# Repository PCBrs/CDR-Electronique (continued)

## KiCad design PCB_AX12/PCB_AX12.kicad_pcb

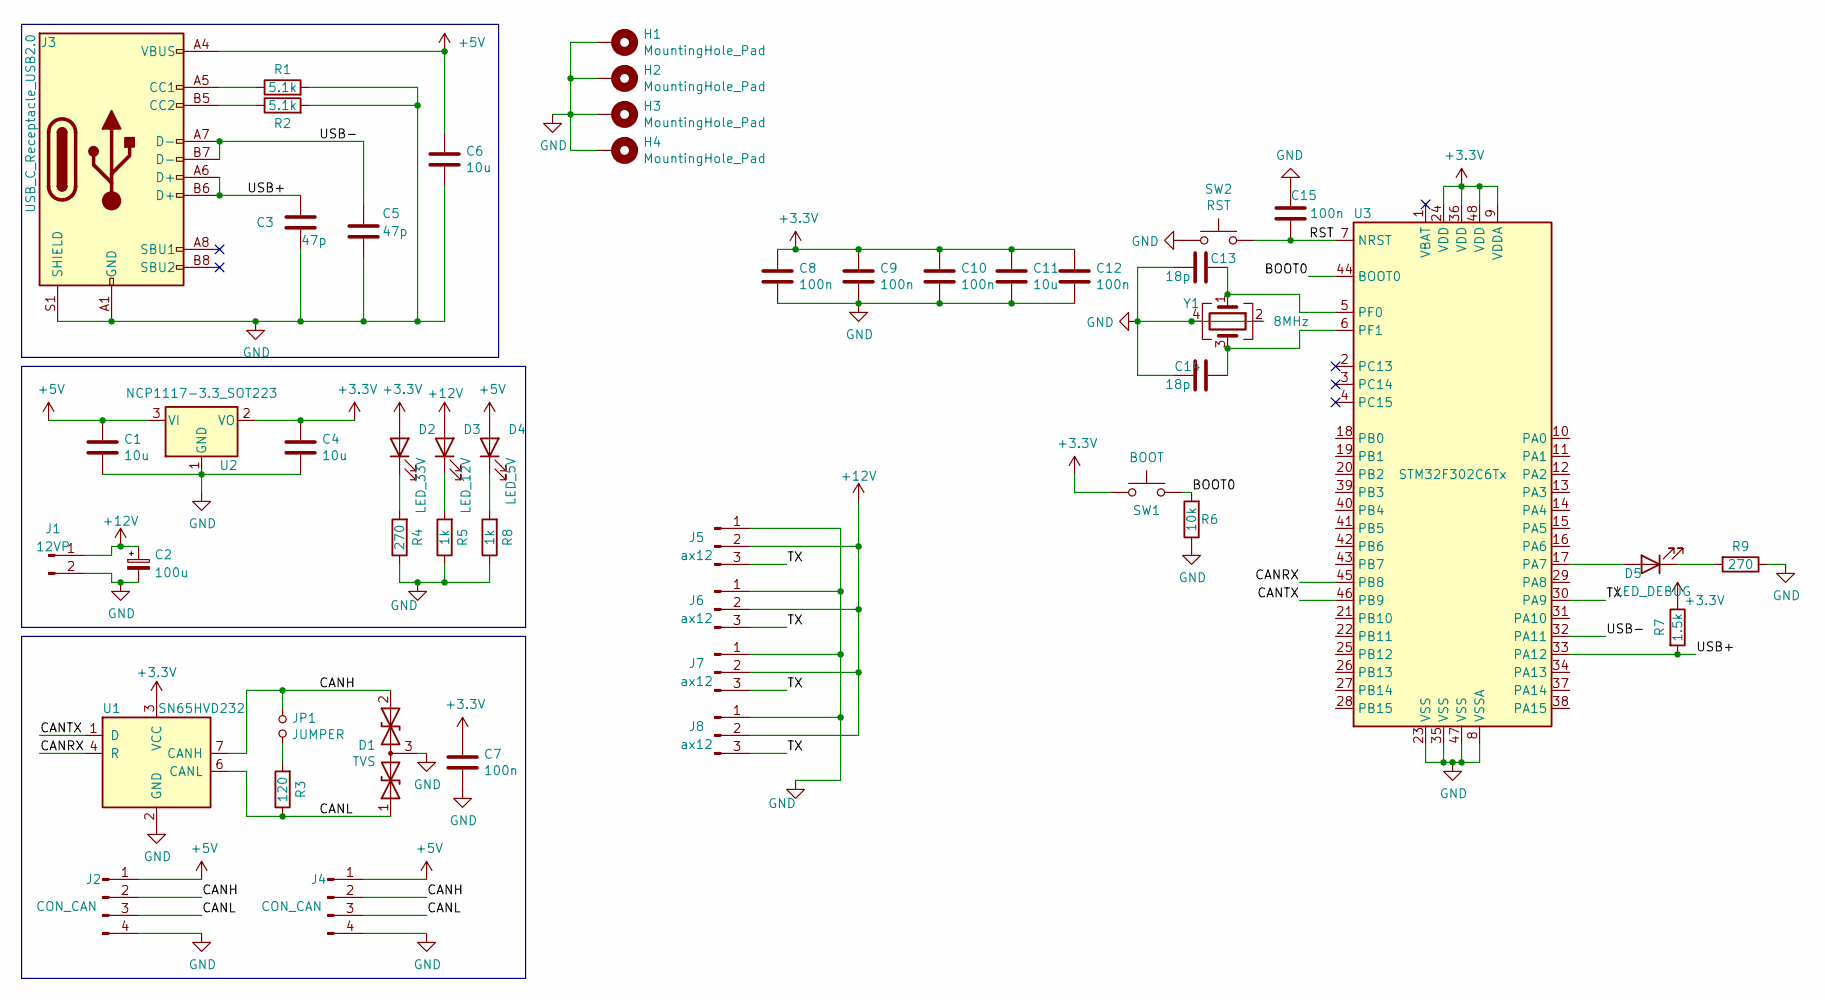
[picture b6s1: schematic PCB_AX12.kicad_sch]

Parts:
C1, C4, C6, C11: 10u; C_0805_2012Metric_Pad1.18x1.45mm_HandSolder
C2: 100u; CP_Radial_D10.0mm_P5.00mm
C3, C5: 47p; C_0805_2012Metric_Pad1.18x1.45mm_HandSolder
C7, C8, C9, C10, C12, C15: 100n; C_0805_2012Metric_Pad1.18x1.45mm_HandSolder
C13, C14: 18p; C_0805_2012Metric_Pad1.18x1.45mm_HandSolder
D1: TVS; SOT-23
D2: LED_33V; LED_0805_2012Metric_Pad1.15x1.40mm_HandSolder
D3: LED_12V; LED_0805_2012Metric_Pad1.15x1.40mm_HandSolder
D4: LED_5V; LED_0805_2012Metric_Pad1.15x1.40mm_HandSolder
D5: LED_DEBUG; LED_0805_2012Metric_Pad1.15x1.40mm_HandSolder
H1, H2, H3, H4: MountingHole_Pad; MountingHole_3.2mm_M3_Pad_Via
J1: 12VP; Wuerth_3.96mm_2pin_645002114822
J2, J4: CON_CAN; 690367290476
J3: USB_C_Receptacle_USB2.0; USB_C_Receptacle_GCT_USB4085
J5, J6, J7, J8: ax12; Molex_SPOX_5267-03A_1x03_P2.50mm_Vertical
JP1: JUMPER; PinHeader_1x02_P2.54mm_Vertical
R1, R2: 5.1k; R_0805_2012Metric_Pad1.20x1.40mm_HandSolder
R3: 120; R_0805_2012Metric_Pad1.20x1.40mm_HandSolder
R4, R9: 270; R_0805_2012Metric_Pad1.20x1.40mm_HandSolder
R5, R8: 1k; R_0805_2012Metric_Pad1.20x1.40mm_HandSolder
R6: 10k; R_0805_2012Metric_Pad1.20x1.40mm_HandSolder
R7: 1.5k; R_0805_2012Metric_Pad1.20x1.40mm_HandSolder
SW1: BOOT; SW_SPST_CK_RS282G05A3
SW2: RST; SW_SPST_CK_RS282G05A3
U1: SN65HVD232; SOIC-8_3.9x4.9mm_P1.27mm
U2: NCP1117-3.3_SOT223; SOT-223-3_TabPin2
U3: STM32F302C6Tx; LQFP-48_7x7mm_P0.5mm
Y1: 8MHz; Crystal_SMD_5032-4Pin_5.0x3.2mm

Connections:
+3V3: C4.1, C7.1, C8.1, C9.1, C10.1, C11.1, C12.1, D2.2 (A), R7.1, SW1.1, U1.3 (VCC), U2.2 (VO), U3.9 (VDDA), U3.24 (VDD), U3.36 (VDD), U3.48 (VDD); also elsewhere on the board
+5V: C1.1, C6.1, D4.2 (A), J2.1, J3.A4 (VBUS), J3.A9 (VBUS), J3.B4 (VBUS), J3.B9 (VBUS), J4.1, U2.3 (VI)
+12V: C2.1, D3.2 (A), J1.1, J5.2, J6.2, J7.2, J8.2
/BOOT0: R6.2, SW1.2, U3.44 (BOOT0); also elsewhere on the board
/CANH: D1.2 (A2), J2.2, J4.2, JP1.1, U1.7 (CANH)
/CANL: D1.1 (A1), J2.3, J4.3, R3.1, U1.6 (CANL)
/CANRX: U1.4 (R), U3.45 (PB8)
/CANTX: U1.1 (D), U3.46 (PB9)
/RST: C15.1, SW2.2, U3.7 (NRST); also elsewhere on the board
/TX: J5.3, J6.3, J7.3, J8.3, U3.30 (PA9)
/USB+: C3.1, J3.A6 (D+), J3.B6 (D+), R7.2, U3.33 (PA12)
/USB-: C5.1, J3.A7 (D-), J3.B7 (D-), U3.32 (PA11)
GND: C1.2, C2.2, C3.2, C4.2, C5.2, C6.2, C7.2, C8.2, C9.2, C10.2, C11.2, C12.2, C13.2, C14.2, C15.2, D1.3 (common), H1.1, H2.1, H3.1, H4.1, J1.2, J2.4, J3.A1 (GND), J3.A12 (GND), J3.B1 (GND), J3.B12 (GND), J3.S1 (SHIELD), J4.4, J5.1, J6.1, J7.1, J8.1, R1.2, R2.2, R4.1, R5.1, R6.1, R8.1, R9.1, SW2.1, U1.2 (GND), U2.1 (GND), U3.8 (VSSA), U3.23 (VSS), U3.35 (VSS), U3.47 (VSS), Y1.2, Y1.4; also elsewhere on the board
unnamed: C13.1, U3.5 (PF0), Y1.1
unnamed: C14.1, U3.6 (PF1), Y1.3
unnamed: D2.1 (K), R4.2
unnamed: D3.1 (K), R5.2
unnamed: D4.1 (K), R8.2
unnamed: D5.1 (K), R9.2
unnamed: J3.A5 (CC1), R1.1
unnamed: J3.B5 (CC2), R2.1
unnamed: JP1.2, R3.2
unnamed: D5.2 (A), U3.17 (PA7)

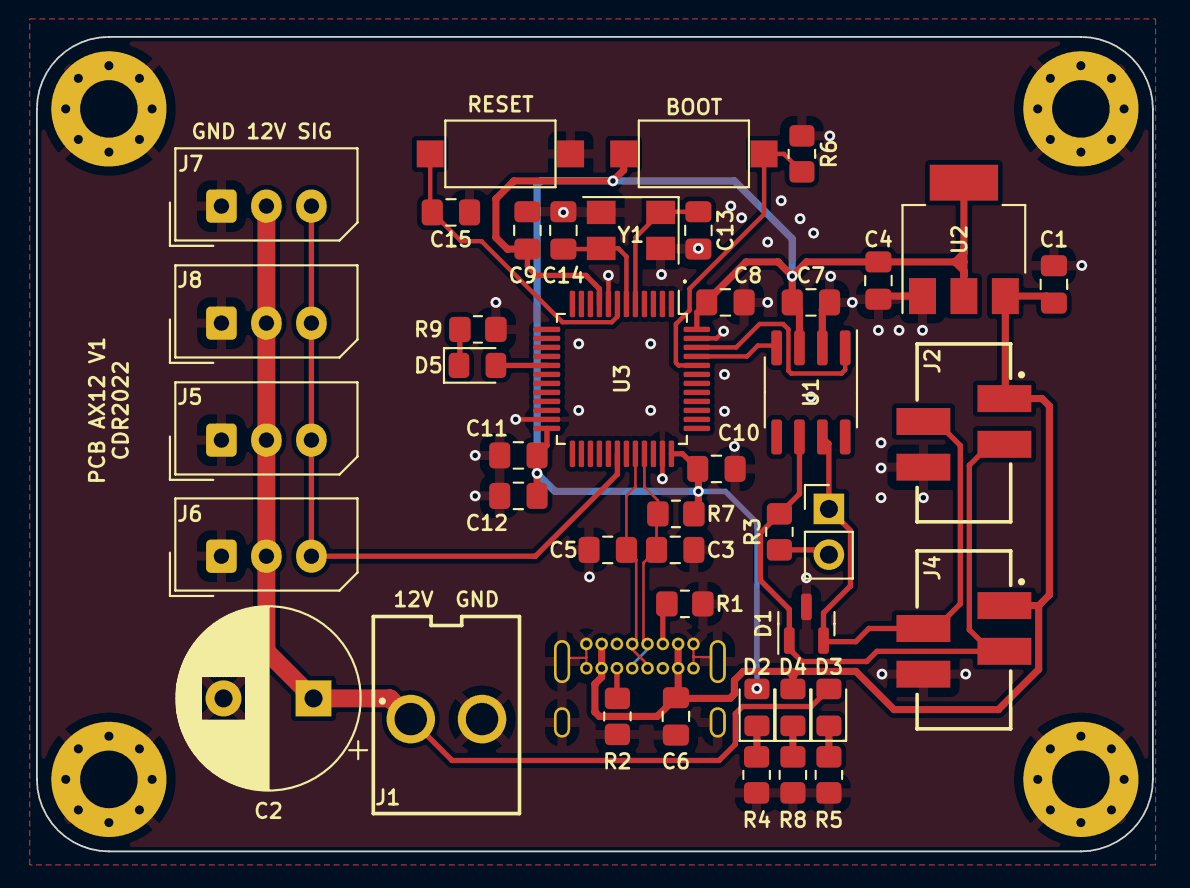
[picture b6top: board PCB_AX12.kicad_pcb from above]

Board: 2 copper layers, 62.0 x 45.2 mm, 48 parts (1 on the bottom side), 23 nets.

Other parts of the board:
BOOT: BOOT; SW_SPST_CK_RS282G05A3
RESET: RST; SW_SPST_CK_RS282G05A3

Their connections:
+3V3: BOOT.1; also elsewhere on the board
/BOOT0: BOOT.2; also elsewhere on the board
/RST: RESET.2; also elsewhere on the board
GND: RESET.1; also elsewhere on the board

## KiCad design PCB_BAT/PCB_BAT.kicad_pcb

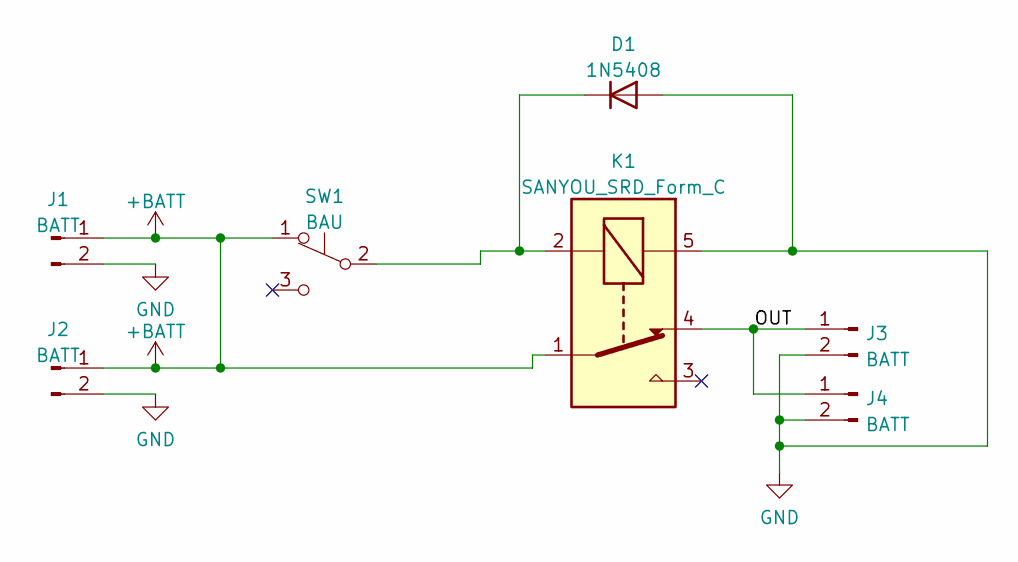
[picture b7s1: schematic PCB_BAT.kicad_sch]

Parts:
D1: 1N5408; D_DO-201AD_P15.24mm_Horizontal
J1, J2: BATT; AMASS_XT60-M_1x02_P7.20mm_Vertical
J3, J4: BATT; Wuerth_batcon_691313710002
K1: SANYOU_SRD_Form_C; Relay_SPDT_SANYOU_SRD_Series_Form_C
SW1: BAU; PinHeader_1x03_P2.54mm_Vertical

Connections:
+BATT: J1.1, J2.1, K1.1, SW1.1 (A)
/OUT: J3.1, J4.1, K1.4
GND: D1.2 (A), J1.2, J2.2, J3.2, J4.2, K1.5
unnamed: D1.1 (K), K1.2, SW1.2 (B)

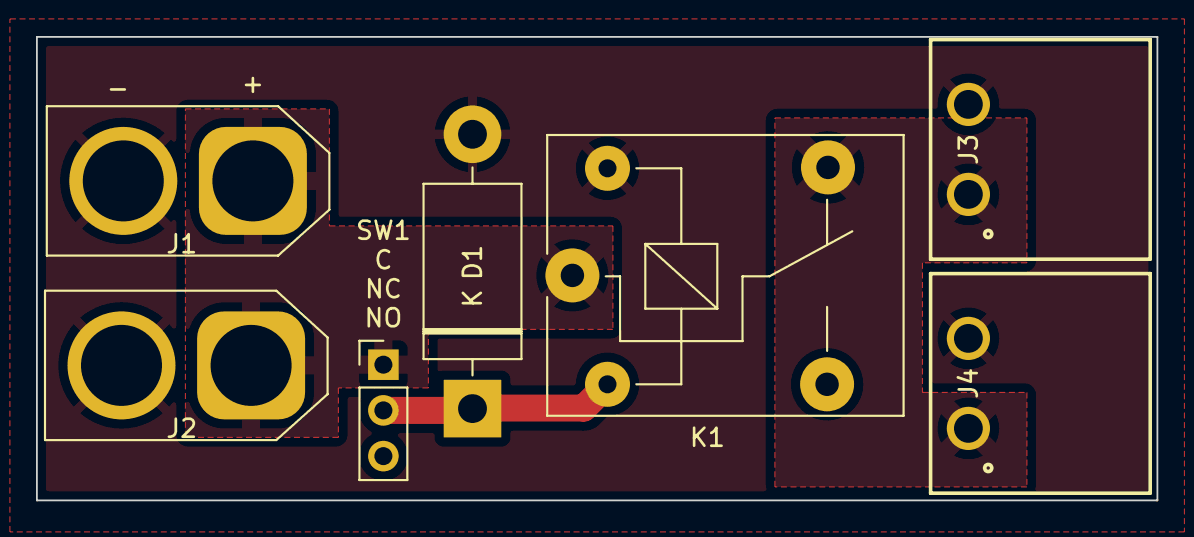
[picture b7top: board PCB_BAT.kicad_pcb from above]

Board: 2 copper layers, 62.2 x 25.8 mm, 7 parts (0 on the bottom side), 4 nets.

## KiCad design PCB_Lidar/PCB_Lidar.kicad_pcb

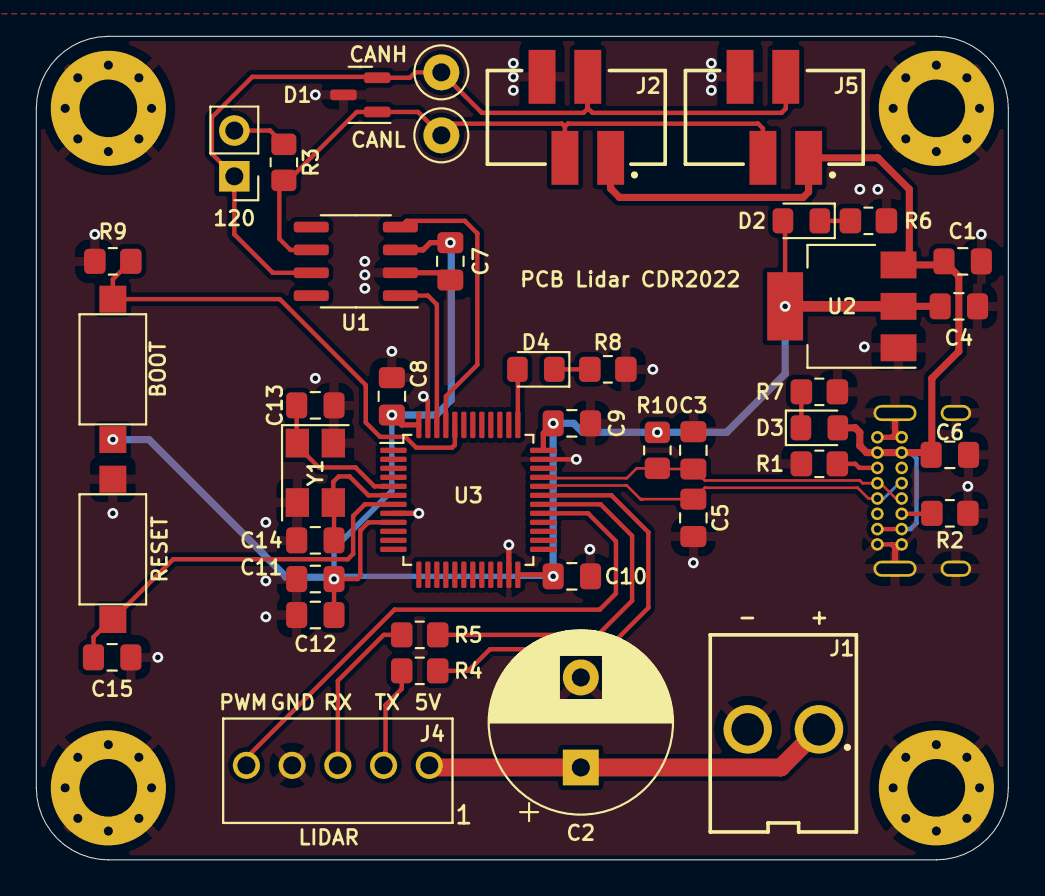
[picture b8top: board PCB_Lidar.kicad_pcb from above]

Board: 2 copper layers, 54.0 x 45.8 mm, 47 parts (1 on the bottom side), 26 nets.

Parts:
120: JUMPER; PinHeader_1x02_P2.54mm_Vertical
BOOT: BOOT; SW_SPST_CK_RS282G05A3
C1, C4, C6, C11: 10u; C_0805_2012Metric_Pad1.18x1.45mm_HandSolder
C2: 100u; CP_Radial_D10.0mm_P5.00mm
C3, C5: 47p; C_0805_2012Metric_Pad1.18x1.45mm_HandSolder
C7, C8, C9, C10, C12, C15: 100n; C_0805_2012Metric_Pad1.18x1.45mm_HandSolder
C13, C14: 18p; C_0805_2012Metric_Pad1.18x1.45mm_HandSolder
CANH: TestPoint; TestPoint_Loop_D1.80mm_Drill1.0mm_Beaded
CANL: TestPoint; TestPoint_Loop_D1.80mm_Drill1.0mm_Beaded
D1: TVS; SOT-23
D2: LED_33V; LED_0805_2012Metric_Pad1.15x1.40mm_HandSolder
D3: LED_5V; LED_0805_2012Metric_Pad1.15x1.40mm_HandSolder
D4: LED_DEBUG; LED_0805_2012Metric_Pad1.15x1.40mm_HandSolder
H1, H2, H3, H4: MountingHole_Pad; MountingHole_3.2mm_M3_Pad_Via
J1: 5VP; Wuerth_3.96mm_2pin_645002114822
J2, J5: CON_CAN; 690367290476
J3: USB_C_Receptacle_USB2.0; USB_C_Receptacle_GCT_USB4085
J4: CON_LIDAR; Wuerth_2.54mm_5pins_61900511121
R1, R2: 5.1k; R_0805_2012Metric_Pad1.20x1.40mm_HandSolder
R3: 120; R_0805_2012Metric_Pad1.20x1.40mm_HandSolder
R4, R5: 33; R_0805_2012Metric_Pad1.20x1.40mm_HandSolder
R6, R8: 270; R_0805_2012Metric_Pad1.20x1.40mm_HandSolder
R7: 560; R_0805_2012Metric_Pad1.20x1.40mm_HandSolder
R9: 10k; R_0805_2012Metric_Pad1.20x1.40mm_HandSolder
R10: 1.5k; R_0805_2012Metric_Pad1.20x1.40mm_HandSolder
RESET: RST; SW_SPST_CK_RS282G05A3
U1: SN65HVD232; SOIC-8_3.9x4.9mm_P1.27mm
U2: NCP1117-3.3_SOT223; SOT-223-3_TabPin2
U3: STM32F302C6Tx; LQFP-48_7x7mm_P0.5mm
Y1: 8MHz; Crystal_SMD_5032-4Pin_5.0x3.2mm

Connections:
+3V3: BOOT.1, C4.1, C7.1, C8.1, C9.1, C10.1, C11.1, C12.1, D2.2 (A), R10.1, U1.3 (VCC), U2.2 (VO), U3.9 (VDDA), U3.24 (VDD), U3.36 (VDD), U3.48 (VDD)
+5P: C2.1, J1.1, J4.1
+5V: C1.1, C6.1, D3.2 (A), J2.1, J3.A4 (VBUS), J3.A9 (VBUS), J3.B4 (VBUS), J3.B9 (VBUS), J5.1, U2.3 (VI)
/BOOT0: BOOT.2, R9.2, U3.44 (BOOT0)
/CANH: 120.1, CANH.1, D1.2 (A2), J2.2, J5.2, U1.7 (CANH)
/CANL: CANL.1, D1.1 (A1), J2.3, J5.3, R3.1, U1.6 (CANL)
/CANRX: U1.4 (R), U3.45 (PB8)
/CANTX: U1.1 (D), U3.46 (PB9)
/MOT_CONTROL: J4.5, U3.29 (PA8)
/RST: C15.1, RESET.2, U3.7 (NRST)
/RX: R4.2, U3.31 (PA10)
/TX: R5.2, U3.30 (PA9)
/USB+: C3.1, J3.A6 (D+), J3.B6 (D+), R10.2, U3.33 (PA12)
/USB-: C5.1, J3.A7 (D-), J3.B7 (D-), U3.32 (PA11)
GND: C1.2, C2.2, C3.2, C4.2, C5.2, C6.2, C7.2, C8.2, C9.2, C10.2, C11.2, C12.2, C13.2, C14.2, C15.2, D1.3 (common), H1.1, H2.1, H3.1, H4.1, J1.2, J2.4, J3.A1 (GND), J3.A12 (GND), J3.B1 (GND), J3.B12 (GND), J3.S1 (SHIELD), J4.4, J5.4, R1.2, R2.2, R6.1, R7.1, R8.1, R9.1, RESET.1, U1.2 (GND), U2.1 (GND), U3.8 (VSSA), U3.23 (VSS), U3.35 (VSS), U3.47 (VSS), Y1.2, Y1.4
unnamed: C13.1, U3.5 (PF0), Y1.1
unnamed: C14.1, U3.6 (PF1), Y1.3
unnamed: D2.1 (K), R6.2
unnamed: D3.1 (K), R7.2
unnamed: D4.1 (K), R8.2
unnamed: J3.A5 (CC1), R1.1
unnamed: J3.B5 (CC2), R2.1
unnamed: J4.2, R4.1
unnamed: J4.3, R5.1
unnamed: 120.2, R3.2
unnamed: D4.2 (A), U3.37 (PA14)
